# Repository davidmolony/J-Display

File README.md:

# J-Display
Basically a display for Jens/MESC project that connects to just about everything with everything.

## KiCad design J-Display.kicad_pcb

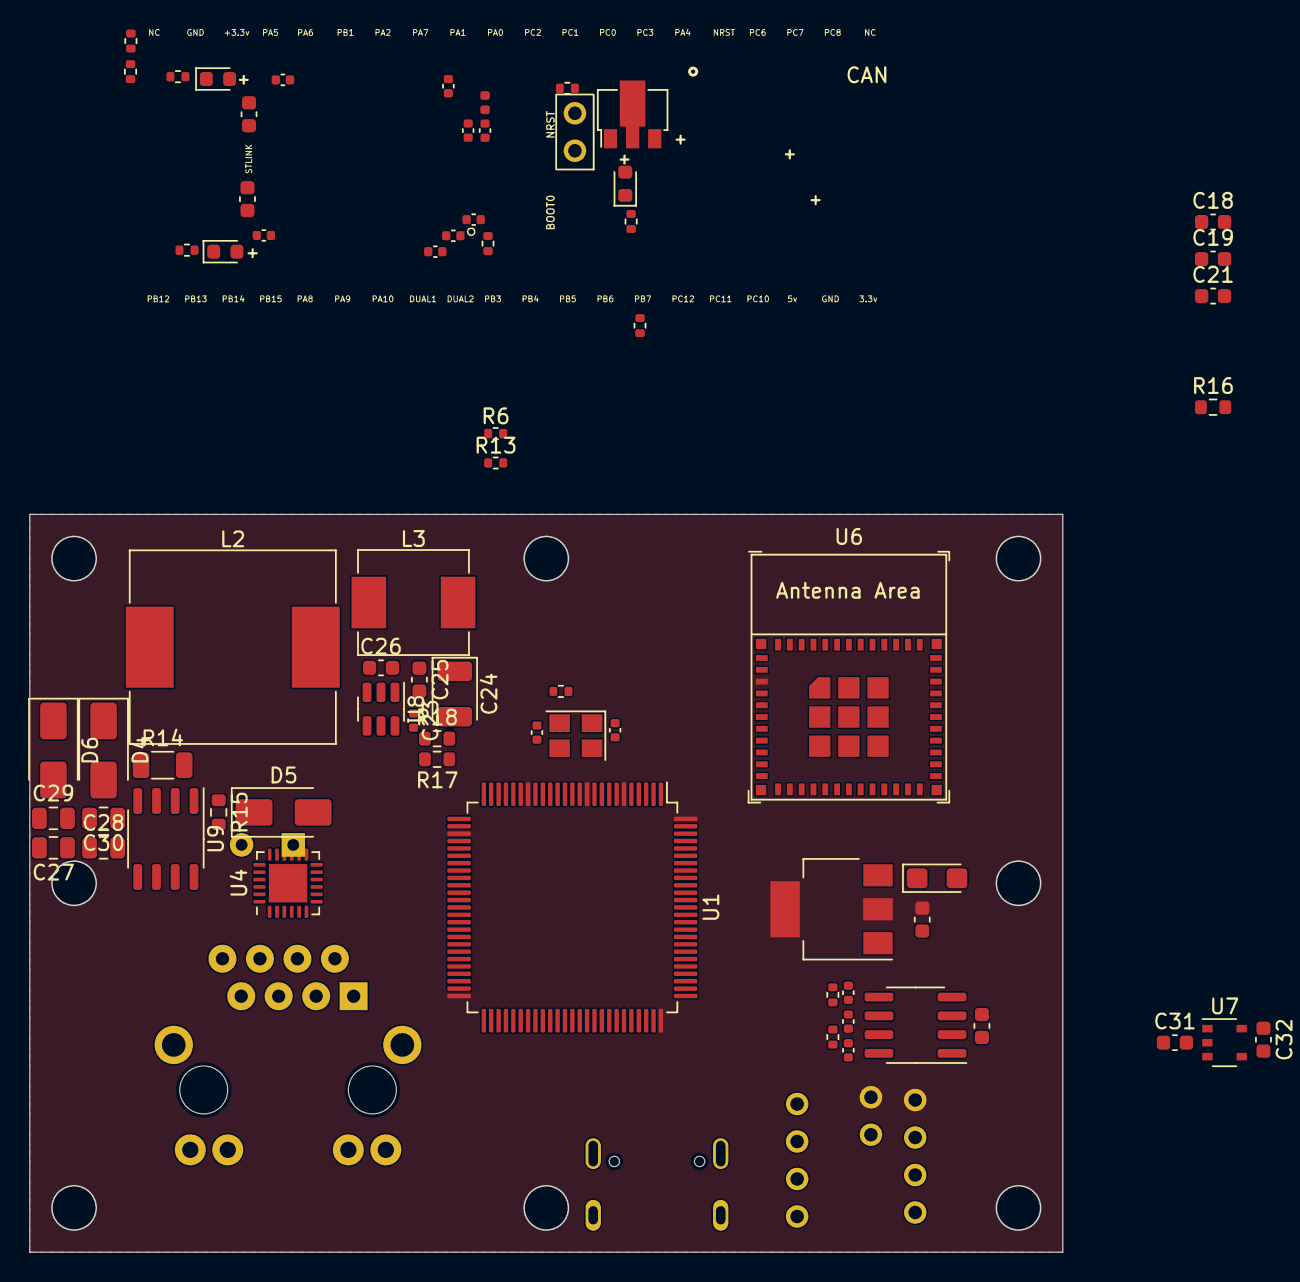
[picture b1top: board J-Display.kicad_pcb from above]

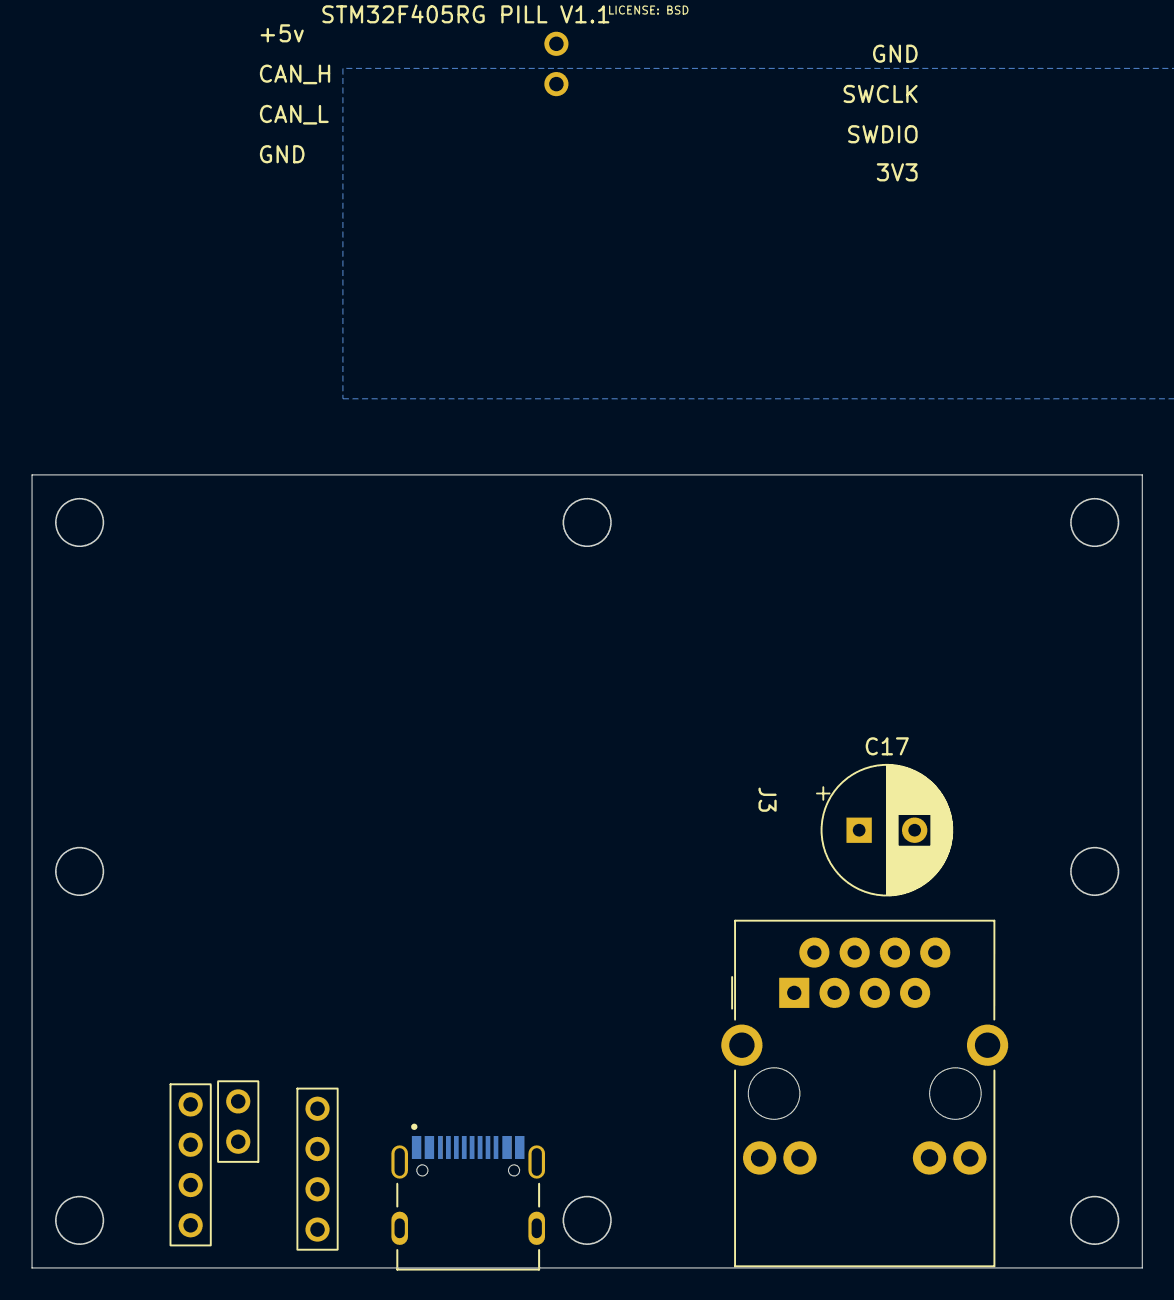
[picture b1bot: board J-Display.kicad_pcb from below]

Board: 4 copper layers, 70.0 x 50.0 mm, 75 parts (6 on the bottom side), 57 nets, no tracks yet.

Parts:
C1: 4u7; C_0402_1005Metric
C2, C4, C7, C10, C12: 100n; C_0402_1005Metric
C3, C6: 12p; C_0402_1005Metric
C5: 1u; C_0402_1005Metric
C8: 10n; C_0402_1005Metric
C9, C11: 2u2; C_0603_1608Metric
C13: 4.7n; C_0402_1005Metric
C14, C15: 100p; C_0402_1005Metric
C16, C22: 10u; C_0603_1608Metric
C17: C_Polarized; CP_Radial_D8.0mm_P3.50mm
C18, C19, C21, C25, C26, C31, C32: C_Small; C_0603_1608Metric
C20: 100n; CP_EIA-3216-18_Kemet-A
C23: C_Small; C_0402_1005Metric
C24: C_Polarized; CP_EIA-3528-21_Kemet-B
C27, C28, C29, C30: C_1u_100V; C_0805_2012Metric
D1: BLU; LED_0603_1608Metric
D2: GRN; LED_0603_1608Metric
D3: RED; LED_0603_1608Metric
D4, D5, D6: D_Small; D_SMA
J1, J2: Conn_01x04_Male; my_4_pin
J3: RJ45_Bel_SI-60062-F
J4: TYPE-C-31-M-12; HRO_TYPE-C-31-M-12
JP1, JP2: Jumper_2_Open; my_2_pin
L1: 39n; L_0402_1005Metric
L2: L_Small; L_Sunlord_MWSA1206S-470
L3: L_Small; L_Sunlord_MWSA0624S
R1, R2: 10k; R_0402_1005Metric
R3, R4: 100Ω; R_0402_1005Metric
R5, R6, R7, R9, R13: 20k; R_0402_1005Metric
R8, R12: 1k; R_0402_1005Metric
R10, R11: 5.1k; R_0402_1005Metric
R14: R_Small; R_1206_3216Metric
R15, R16, R17, R18: R_Small; R_0603_1608Metric
U1: STM32F407VGTx; LQFP-100_14x14mm_P0.5mm
U2: TJA1050T/CM,118; SOIC-8_3.9x4.9mm_P1.27mm
U3: LM1117-3.3; SOT-223-3_TabPin2
U4: LAN8720A; QFN-24-1EP_4x4mm_P0.5mm_EP2.6x2.6mm
U5: HT7550; SOT-89-3
U6: ESP32-C3-MINI-1
U7: NCS20071SN; TSOP-5_1.65x3.05mm_P0.95mm
U8: TPS563200; SOT-23-6
U9: SO-8_3.9x4.9mm_P1.27mm
Y1: Crystal_GND24; Crystal_SMD_3225-4Pin_3.2x2.5mm

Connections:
5V_VFB: R17.2, R18.1, U8.4 (VFB)
+3.3VA: C5.1, C8.1, L1.2, U1.21 (VREF+), U1.22 (VDDA)
+3V3: C1.1, C2.1, C4.1, C7.1, C10.1, C12.1, C22.1, C32.1, D1.2 (A), J2.4, JP1.1 (A), L1.1, R2.1, U1.6 (VBAT), U1.11 (VDD), U1.19 (VDD), U1.28 (VDD), U1.50 (VDD), U1.75 (VDD), U1.100 (VDD), U3.2 (VO), U6.3 (3V3), U7.5 (V+)
+5V: C20.1, J1.4, J4.A4B9 (VBUS), J4.B4A9 (VBUS), U3.3 (VI), U5.2 (VI)
+12V: C17.1, C18.1, C26.1, D5.2 (A), L2.2, U8.3 (VIN), U8.5 (EN)
DUAL1: R8.1, U1.47 (PB10)
ETH_CRS_DV: U1.32 (PA7), U4.11 (CRS_DV/MODE2)
ETH_MDIO: U1.25 (PA2), U4.12 (MDIO)
ETH_REF_CLK: U1.24 (PA1), U4.14 (INT/REFCLKO)
ETH_RXD0: U1.33 (PC4), U4.8 (RXD0/MODE0)
ETH_RXD1: U1.34 (PC5), U4.7 (RXD1/MODE1)
ETH_TXD0: U1.51 (PB12), U4.17 (TXD0)
ETH_TXD1: U1.52 (PB13), U4.18 (TXD1)
ETH_TX_EN: U1.48 (PB11), U4.16 (TXEN)
GND: C1.2, C2.2, C3.2, C4.2, C5.2, C6.2, C7.2, C8.2, C9.2, C10.2, C11.2, C12.2, C13.2, C14.2, C15.2, C16.2, C17.2, C18.2, C20.2, C22.2, C24.2, C25.2, C26.2, C29.2, C30.2, C31.2, C32.2, D4.2 (A), D6.2 (A), J1.1, J2.1, J3.8 (GND), J3.SH (SHIELD), J4.A1B12 (GND), J4.B1A12 (GND), J4.S1 (SHIELD), J4.S2 (SHIELD), J4.S3 (SHIELD), J4.S4 (SHIELD), JP2.2 (B), R1.1, R5.1, R6.1, R7.1, R9.1, R10.2, R11.2, R13.1, R18.2, U1.10 (VSS), U1.20 (VSSA), U1.27 (VSS), U1.37 (PB2), U1.74 (VSS), U1.99 (VSS), U2.2 (GND), U2.8 (S), U3.1 (GND), U4.25 (VSS), U5.1 (GND), U6.1 (GND), U6.2 (GND), U6.11 (GND), U6.14 (GND), U7.2 (V-), U8.1 (GND), Y1.2, Y1.4
NRST: JP2.1 (A), R2.2, U1.14 (NRST)
unnamed: C13.1, R3.1, R4.2
unnamed: C24.1, C25.1, L3.2, R17.1
unnamed: C27.2, C28.2, C29.1, C30.1
unnamed: D1.1 (K), R9.2
unnamed: D2.1 (K), R5.2
unnamed: D3.1 (K), R7.2
unnamed: C19.2, C21.1, D4.1 (K), D6.1 (K), L2.1, R14.2, R16.2, U9.2 (GND)
unnamed: C19.1, D5.1 (K), R15.1
unnamed: C15.1, J1.2, R4.1, U2.6 (CANL)
unnamed: C14.1, J1.3, R3.2, U2.7 (CANH)
unnamed: J3.L3 (LEDG_A), U4.3 (LED1/REGOFF)
unnamed: J3.L4 (LEDG_K), R6.2
unnamed: J3.L1 (LEDY_A), U4.2 (LED2/nINTSEL)
unnamed: J3.L2 (LEDY_K), R13.2
unnamed: J3.4 (RD+), U4.23 (RXP)
unnamed: J3.6 (RD-), U4.22 (RXN)
unnamed: J3.1 (TD+), U4.21 (TXP)
unnamed: J3.3 (TD-), U4.20 (TXN)
unnamed: J4.A5 (CC1), R10.1
unnamed: J4.B5 (CC2), R11.1
unnamed: JP1.2 (B), R1.2, U1.94 (BOOT0)
unnamed: C3.1, U1.12 (PH0), Y1.1
unnamed: C6.1, U1.13 (PH1), Y1.3
unnamed: C9.1, U1.49 (VCAP_1)
unnamed: C11.1, U1.73 (VCAP_2)
unnamed: U6.36 (GND), U6.37 (GND), U6.38 (GND), U6.39 (GND), U6.40 (GND), U6.41 (GND), U6.42 (GND), U6.43 (GND), U6.44 (GND), U6.45 (GND), U6.46 (GND), U6.47 (GND), U6.48 (GND), U6.49 (GND), U6.50 (GND), U6.51 (GND), U6.52 (GND), U6.53 (GND)
unnamed: C23.1, L3.1, U8.2 (SW)
unnamed: C23.2, U8.6 (VBST)
unnamed: R14.1, U9.4 (CS)
unnamed: R15.2, R16.1, U9.3 (FB)
unnamed: C21.2, U9.1 (VDD)
PA15: D2.2 (A), U1.77 (PA15)
PB8: U1.95 (PB8), U2.4 (RXD)
PB9: U1.96 (PB9), U2.1 (TXD)
PC9: D3.2 (A), U1.66 (PC9)
SWCLK: J2.2, U1.76 (PA14)
SWDIO: J2.3, U1.72 (PA13)
USB_D+: J4.A6 (DP1), J4.B6 (DP2), U1.71 (PA12)
USB_D-: J4.A7 (DN1), J4.B7 (DN2), U1.70 (PA11)
VBUS: C27.1, C28.1, U9.5 (Drain), U9.6 (Drain)
VDO_I: C16.1, U2.3 (VCC), U5.3 (VO)

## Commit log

2023-03-14 Initial commit with start of DCDC, Ethernet, Wifi, CAN, F407VG and the strain guage amplifier

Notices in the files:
J-Display.kicad_pcb:
LICENSE: BSD
